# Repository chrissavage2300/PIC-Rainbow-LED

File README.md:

# PIC-Rainbow-LED
Soft RGB LED Lamp that has an optional battery inside
https://www.youtube.com/watch?v=jD3dlQd_uq0

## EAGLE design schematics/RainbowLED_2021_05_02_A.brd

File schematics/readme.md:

Possible hardware bug with low battery detect circuit. Under some conditions it may allow the battery to be powered, unless my low battery IC is broken.

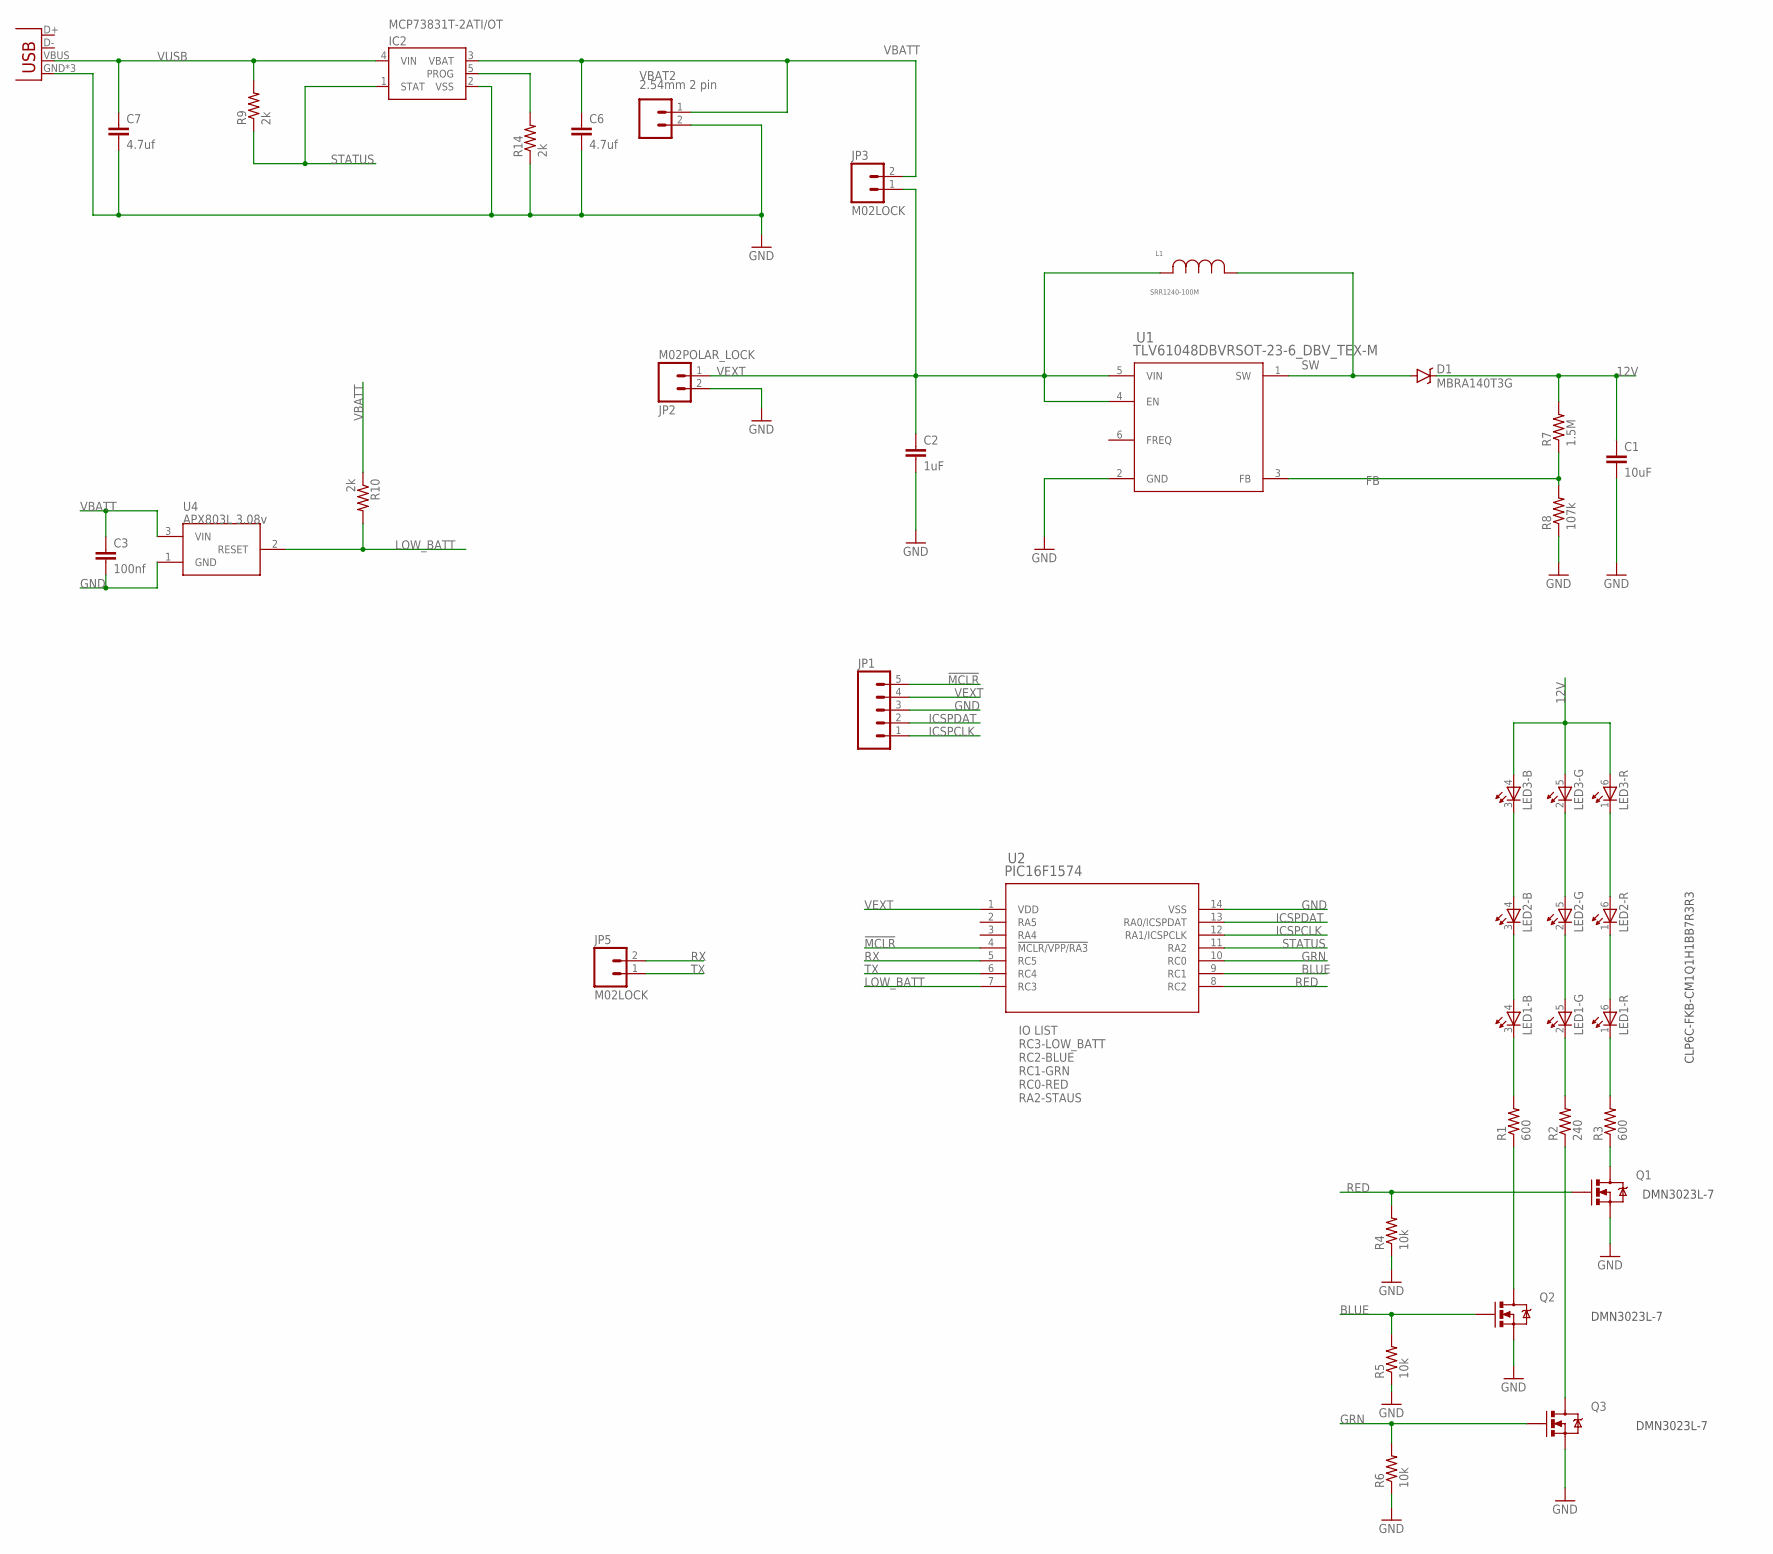
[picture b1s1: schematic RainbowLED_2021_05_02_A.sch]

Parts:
C1: 10uF; 1206
C2: 1uF; 1206
C3: 100nf; 1206
C6, C7: 4.7uf; 1206
D1: MBRA140T3G; SMA-DIODE
IC2: MCP73831T-2ATI/OT; SOT23-5
JP1: M05LOCK; 1X05_LOCK
JP2: M02POLAR_LOCK; MOLEX-1X2_LOCK
JP3, JP5: M02LOCK; 1X02_LOCK
JP4: USB-MICROB
L1: SRR1240-100M; IND_BOURNS_SRR1240
LED1, LED2, LED3: CLX6F-FKC-CKNNQDGBB7A363; PLCC-6
Q1, Q2, Q3: DMN3023L-7; SOT23-3
R1, R3: 600; 1206
R2: 240; 1206
R4, R5, R6: 10k; 1206
R7: 1.5M; 1206
R8: 107k; 1206
R9, R10, R14: 2k; 1206
U1: TLV61048DBVRSOT-23-6_DBV_TEX-M; SOT-23-6_DBV_TEX-M
U2: PIC16F1574; SOIC14_SL
U4: APX803L 3.08v; SOT23
VBAT2: 2.54mm 2 pin; JST-2-PTH-VERT

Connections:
12V: C1.1, D1.C, LED3.4 (A), LED3.5 (A), LED3.6 (A), R7.2
!MCLR: JP1.5, U2.4 (!MCLR/VPP/RA3)
BLUE: Q2.1 (G), R5.2, U2.9 (RC1)
FB: R7.1, R8.2, U1.3 (FB)
GND: C1.2, C2.2, C3.2, C6.2, C7.2, IC2.2 (VSS), JP1.3, JP2.2, JP4.GND, JP4.MT1 (GND), JP4.MT2 (GND), Q1.2 (S), Q2.2 (S), Q3.2 (S), R4.1, R5.1, R6.1, R8.1, R14.1, U1.2 (GND), U2.14 (VSS), U4.1 (GND), VBAT2.2
GRN: Q3.1 (G), R6.2, U2.10 (RC0)
ICSPCLK: JP1.1, U2.12 (RA1/ICSPCLK)
ICSPDAT: JP1.2, U2.13 (RA0/ICSPDAT)
LOW_BATT: R10.2, U2.7 (RC3), U4.2 (RESET)
unnamed: LED2.4 (A), LED3.3 (C)
unnamed: LED1.4 (A), LED2.3 (C)
unnamed: LED2.5 (A), LED3.2 (C)
unnamed: LED1.5 (A), LED2.2 (C)
unnamed: LED2.6 (A), LED3.1 (C)
unnamed: LED1.6 (A), LED2.1 (C)
unnamed: LED1.3 (C), R1.2
unnamed: LED1.2 (C), R2.2
unnamed: LED1.1 (C), R3.2
unnamed: Q1.3 (D), R3.1
unnamed: Q2.3 (D), R1.1
unnamed: Q3.3 (D), R2.1
unnamed: IC2.5 (PROG), R14.2
RED: Q1.1 (G), R4.2, U2.8 (RC2)
RX: JP5.2, U2.5 (RC5)
STATUS: IC2.1 (STAT), R9.1, U2.11 (RA2)
SW: D1.A, L1.1, U1.1 (SW)
TX: JP5.1, U2.6 (RC4)
VBATT: C3.1, C6.1, IC2.3 (VBAT), JP3.2, R10.1, U4.3 (VIN), VBAT2.1
VEXT: C2.1, JP1.4, JP2.1, JP3.1, L1.2, U1.4 (EN), U1.5 (VIN), U2.1 (VDD)
VUSB: C7.1, IC2.4 (VIN), JP4.VBUS, R9.2

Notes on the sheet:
‎CLP6C-FKB-CM1Q1H1BB7R3R3‎
‎DMN3023L-7‎
IO LIST RC3-LOW_BATT RC2-BLUE RC1-GRN RC0-RED RA2-STAUS

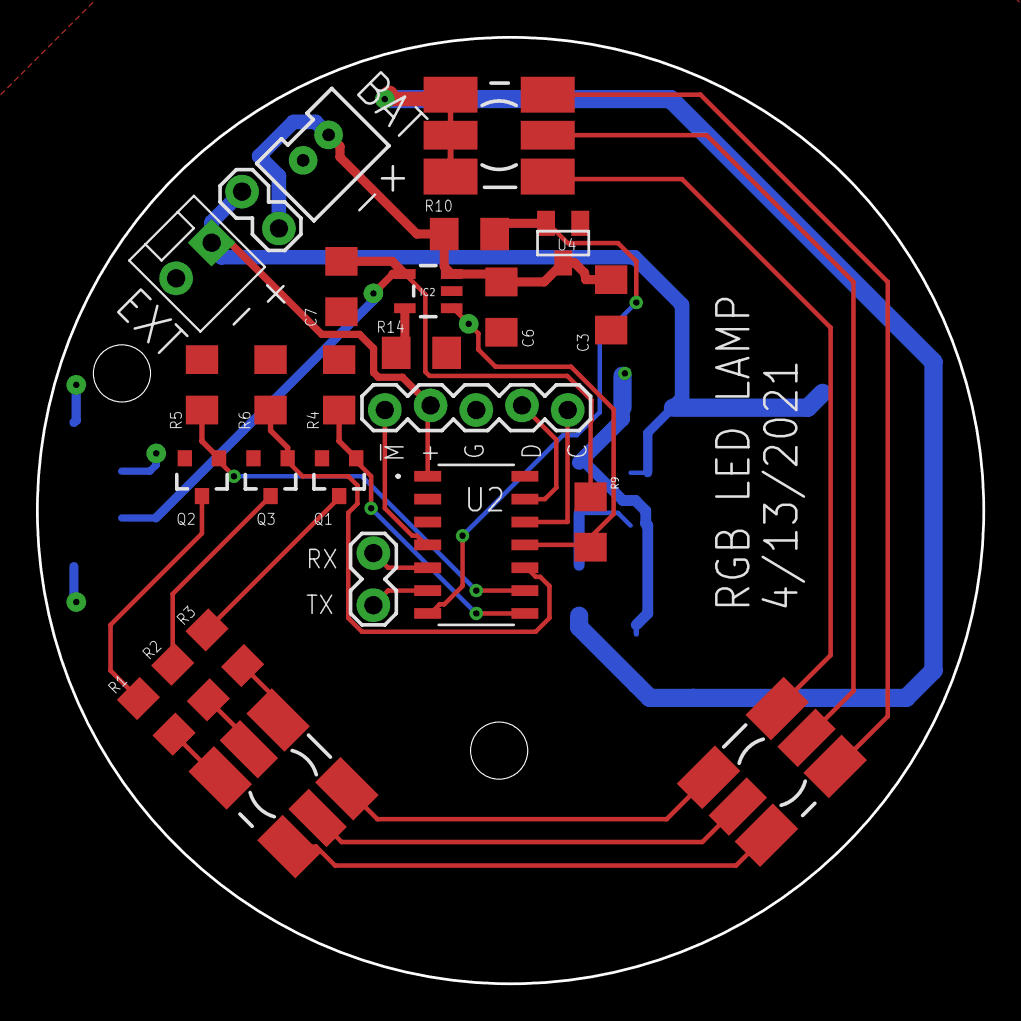
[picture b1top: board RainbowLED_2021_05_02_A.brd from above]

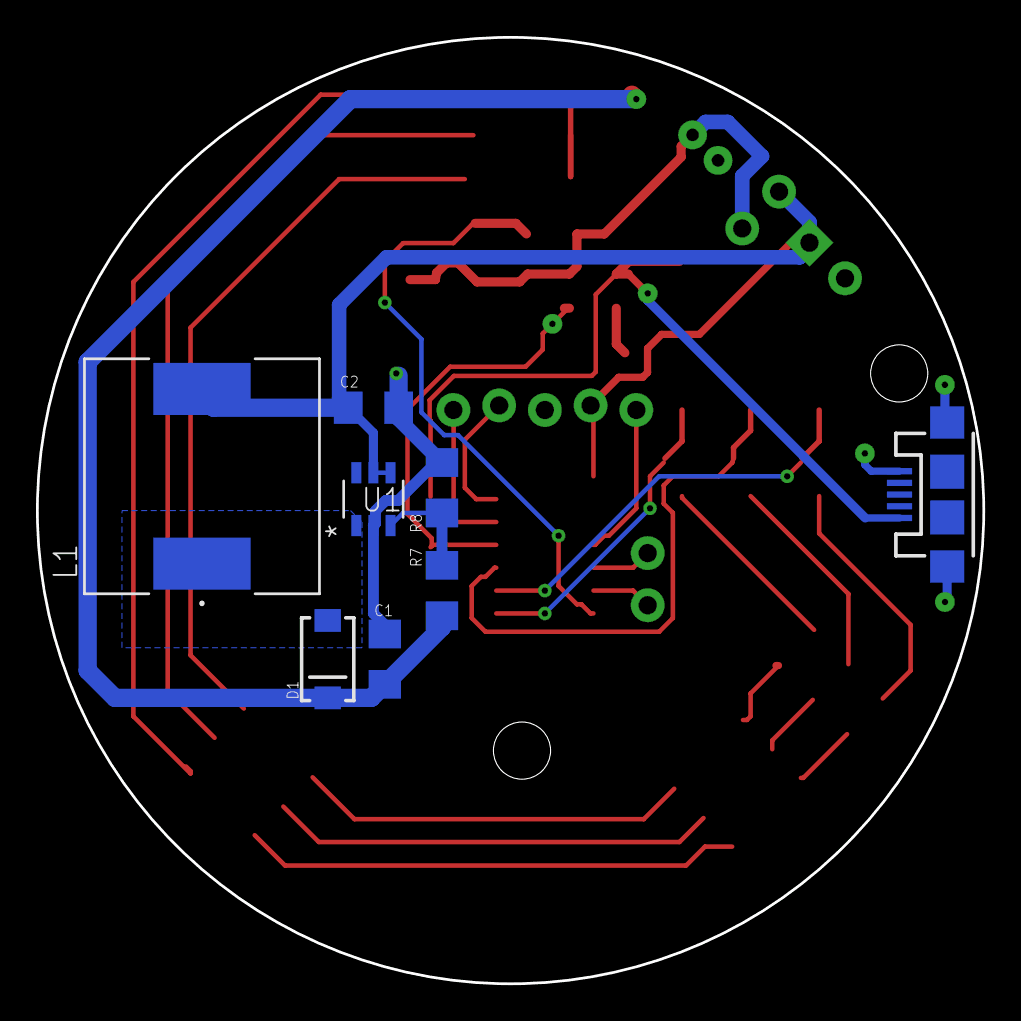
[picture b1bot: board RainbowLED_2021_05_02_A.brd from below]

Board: 2 copper layers, 52.6 x 52.6 mm, 34 parts (8 on the bottom side), 30 nets.

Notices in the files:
parts and their libraries:
SparkFun-Connectors: Licensing: Creative Commons ShareAlike 4.0 International - https://creativecommons.org/licenses/by-sa/4.0
COPYRIGHT: Copyright (C) 2018 Accelerated Designs. All rights reserved
